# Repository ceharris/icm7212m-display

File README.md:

icm7212m-display
===============

A four-digit LED display module based around the Maxim 7212M display
driver.

The ICM7212M is an LED display driver component designed to allow up to
four 7-segment LED displays to be controlled via parallel microprocessor
interface.

This project combines the 40-pin PDIP package for the ICM7212M along with
four 7-segment LED displays, and a trim pot, on a 70mm x 50mm board with 
either pin headers or pin sockets for the bus interface. This allows the 
ICM7212M to be connected directly to the bus of a computer system, 
addressed like any other I/O device, and thus providing an easy-to-use 
hardware display for debugging, status, or other applications.

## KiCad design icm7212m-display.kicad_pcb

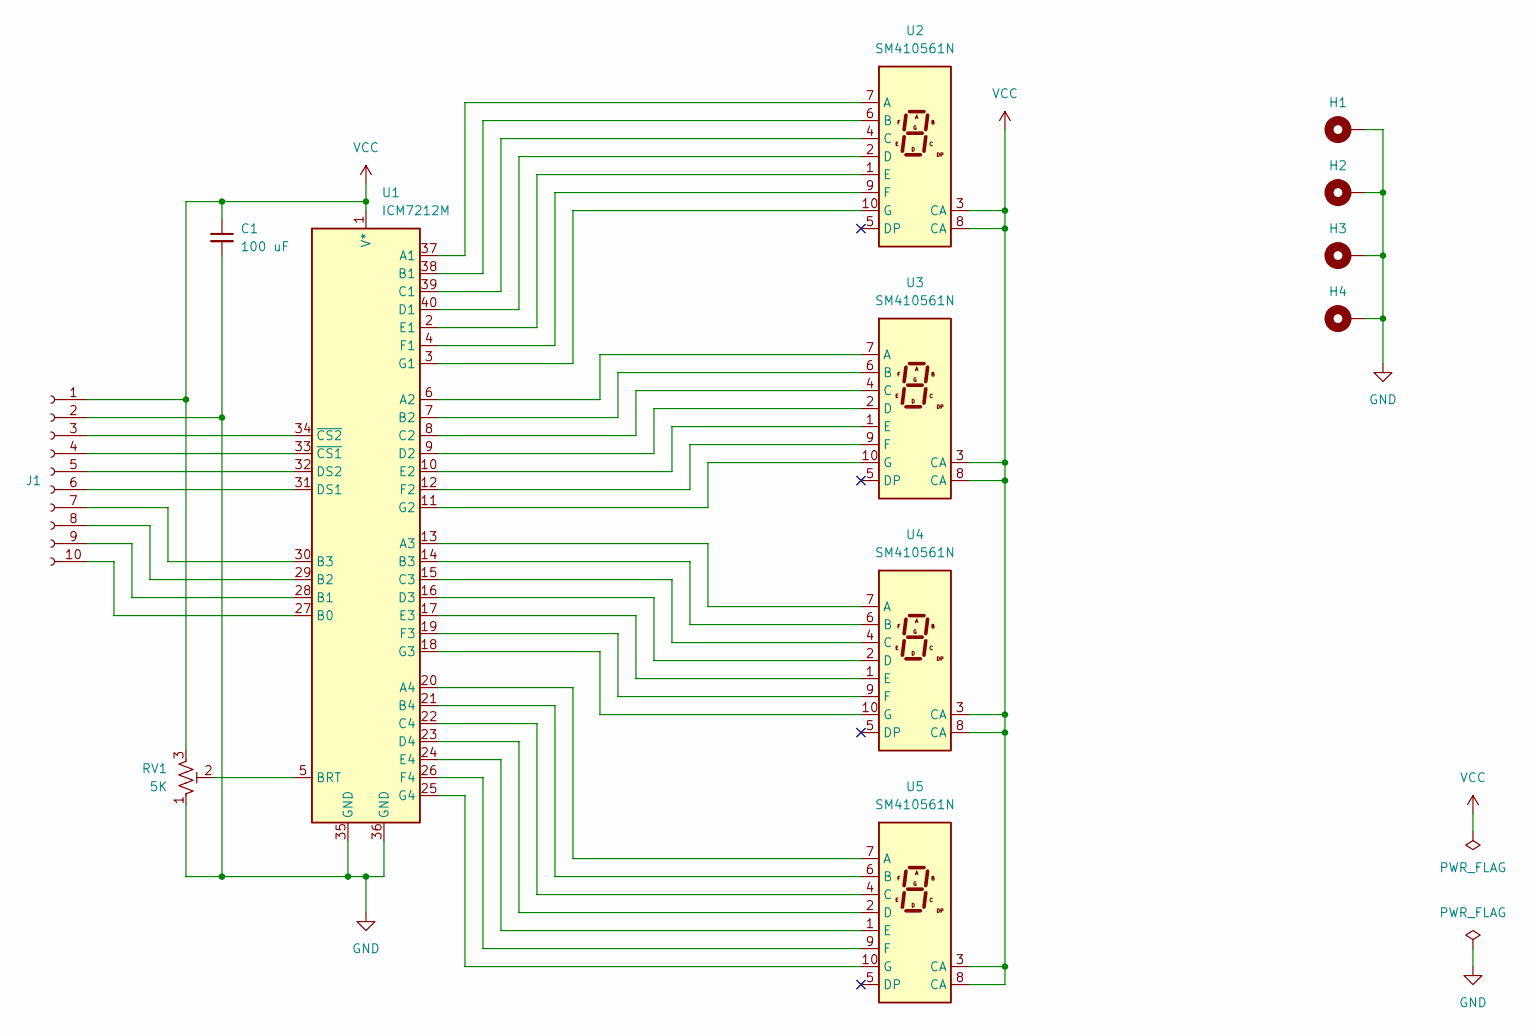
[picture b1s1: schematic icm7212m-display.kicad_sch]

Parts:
C1: 100 uF; C_Disc_D3.0mm_W2.0mm_P2.50mm
H1, H2, H3, H4: MountingHole_Pad; MountingHole_2.2mm_M2_DIN965_Pad
J1: Conn_01x10_Socket; PinSocket_1x10_P2.54mm_Vertical
RV1: 5K; Bochen-3296-Trim-Pot
U1: ICM7212M; DIP-40_W15.24mm_Socket
U2, U3, U4, U5: SM410561N; D1X8K

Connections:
GND: C1.2, H1.1, H2.1, H3.1, H4.1, J1.2, RV1.1, U1.35 (GND), U1.36 (GND)
unnamed: J1.3, U1.34 (~CS2)
unnamed: J1.4, U1.33 (~CS1)
unnamed: J1.5, U1.32 (DS2)
unnamed: J1.6, U1.31 (DS1)
unnamed: J1.7, U1.30 (B3)
unnamed: J1.8, U1.29 (B2)
unnamed: J1.9, U1.28 (B1)
unnamed: J1.10, U1.27 (B0)
unnamed: U1.37 (A1), U2.7 (A)
unnamed: U1.6 (A2), U3.7 (A)
unnamed: U1.13 (A3), U4.7 (A)
unnamed: U1.20 (A4), U5.7 (A)
unnamed: U1.21 (B4), U5.6 (B)
unnamed: RV1.2, U1.5 (BRT)
unnamed: U1.39 (C1), U2.4 (C)
unnamed: U1.8 (C2), U3.4 (C)
unnamed: U1.15 (C3), U4.4 (C)
unnamed: U1.22 (C4), U5.4 (C)
unnamed: U1.40 (D1), U2.2 (D)
unnamed: U1.9 (D2), U3.2 (D)
unnamed: U1.16 (D3), U4.2 (D)
unnamed: U1.23 (D4), U5.2 (D)
unnamed: U1.2 (E1), U2.1 (E)
unnamed: U1.10 (E2), U3.1 (E)
unnamed: U1.17 (E3), U4.1 (E)
unnamed: U1.24 (E4), U5.1 (E)
unnamed: U1.4 (F1), U2.9 (F)
unnamed: U1.12 (F2), U3.9 (F)
unnamed: U1.19 (F3), U4.9 (F)
unnamed: U1.26 (F4), U5.9 (F)
unnamed: U1.3 (G1), U2.10 (G)
unnamed: U1.11 (G2), U3.10 (G)
unnamed: U1.18 (G3), U4.10 (G)
unnamed: U1.25 (G4), U5.10 (G)
unnamed: U1.38 (B1), U2.6 (B)
unnamed: U1.7 (B2), U3.6 (B)
unnamed: U1.14 (B3), U4.6 (B)
VCC: C1.1, J1.1, RV1.3, U1.1 (V*), U2.3 (CA), U2.8 (CA), U3.3 (CA), U3.8 (CA), U4.3 (CA), U4.8 (CA), U5.3 (CA), U5.8 (CA)

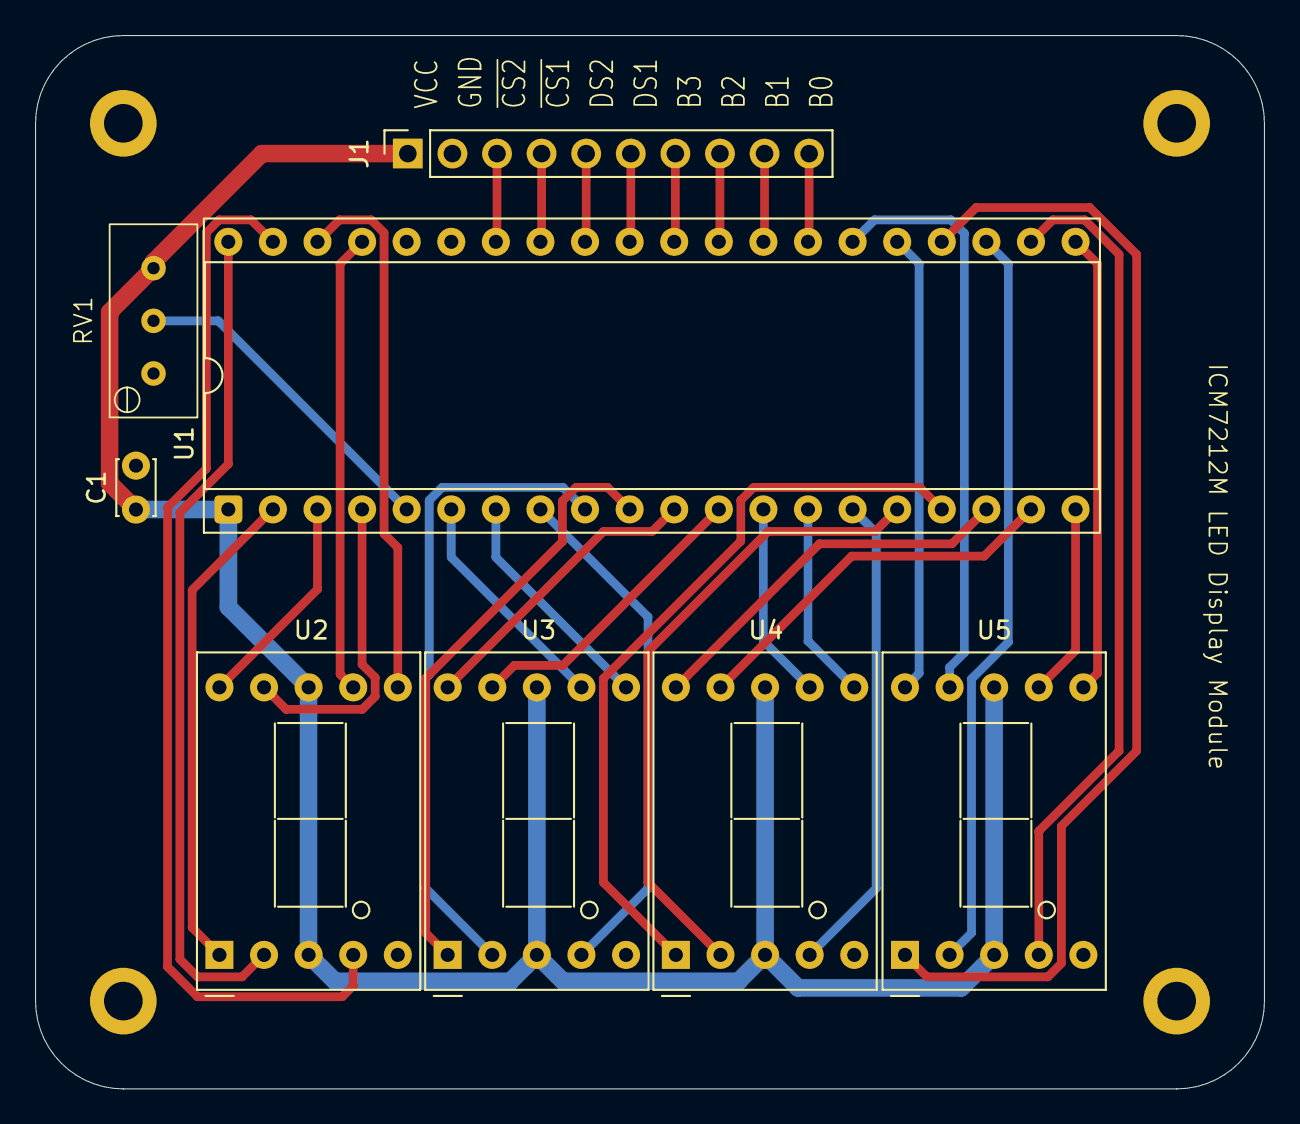
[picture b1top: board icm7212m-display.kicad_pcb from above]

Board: 2 copper layers, 70.0 x 60.0 mm, 12 parts (0 on the bottom side), 39 nets.

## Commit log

2025-06-01 first completion
2025-06-01 README improvements
2025-06-01 additional refinement
2025-06-19 add photo; fix license
2025-06-19 add PDF for the schematic
